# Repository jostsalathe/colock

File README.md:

# Colock
A USB powered RGB wall clock inspired by analog clocks

## Parts

| Part | Count | Refs | JLCPCB # ***extended*** |
| --- | --- | --- | --- |
| 100nF | 61 | C1...60, C63 | C14663 |
| 10uF | 2 | C61, C62 | C19702 |
| SK6812SIDE-A-RVS | 60 | LED1...60 | ***C2890037*** |
| TYPE-C-31-M-17 | 1 | J15 | ***C283540*** |
| AO3400A | 1 | Q1 | C20917 |
| 0R | 1 | R1 | C21189 |
| 2k2 | 1 | R2 | C4190 |
| 10k | 4 | R3...6 | C25804 |
| 5k1 | 2 | R7, R8 | C23186 |
| AMS1117-3.3 | 1 | U1 | C6186 |

## Assembly

You need two panels with one main segment and five LED segments each to for a full circle by soldering all those segments together.

The panels should look a little something like this (don't mind the missing 3D models):

One of the two main segments needs to get the USB-C socket, (optionally the UART header) as well as the ESP-01 Pin-Socket added and the 0 Ohm link R1 removed (if ordered with populated SMD components).

The other main segment may benefit from removing the pullup resistor R2 and the level shifting MOSFET Q1.

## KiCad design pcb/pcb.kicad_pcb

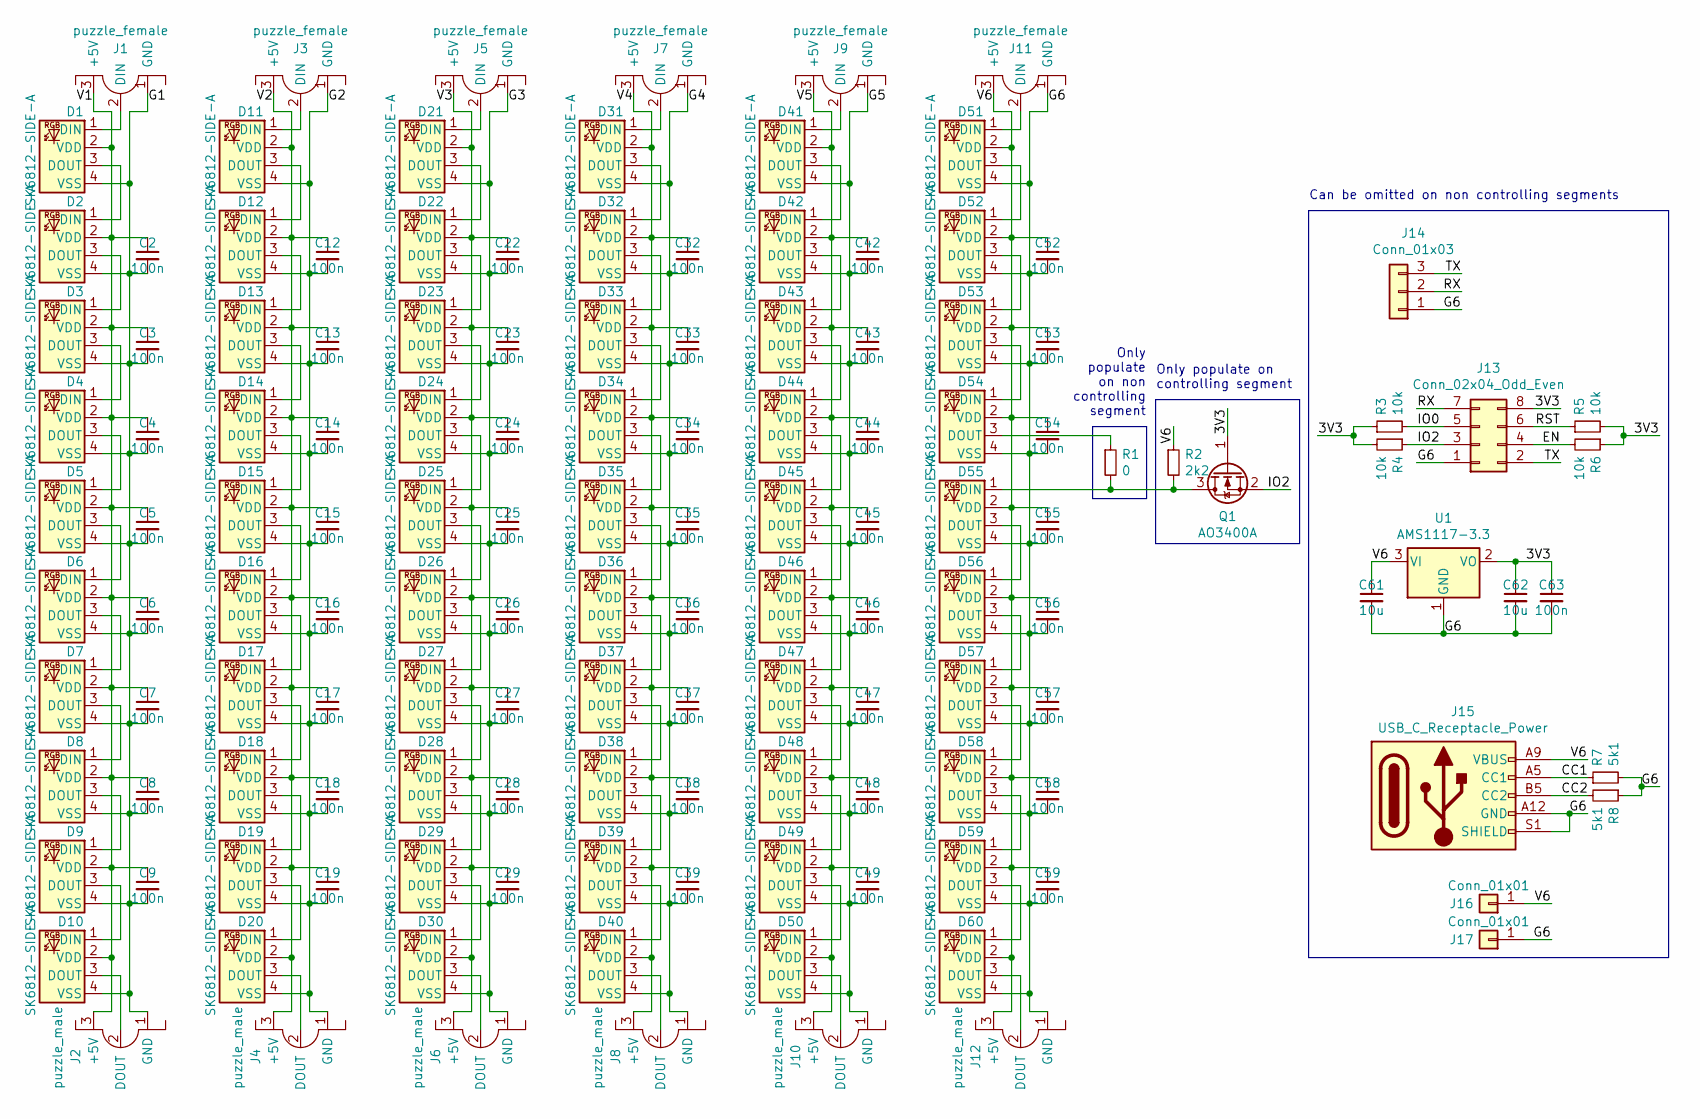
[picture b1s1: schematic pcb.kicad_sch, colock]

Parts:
C2, C3, C4, C5, C6, C7, C8, C9, C12, C13, C14, C15, C16, C17, C18, C19, C22, C23, C24, C25, C26, C27, C28, C29, C32, C33, C34, C35, C36, C37, C38, C39, C42, C43, C44, C45, C46, C47, C48, C49, C52, C53, C54, C55, C56, C57, C58, C59, C63: 100n; C_0603_1608Metric_Pad1.08x0.95mm_HandSolder
C61, C62: 10u; C_0603_1608Metric_Pad1.08x0.95mm_HandSolder
D1, D2, D3, D4, D5, D6, D7, D8, D9, D10, D11, D12, D13, D14, D15, D16, D17, D18, D19, D20, D21, D22, D23, D24, D25, D26, D27, D28, D29, D30, D31, D32, D33, D34, D35, D36, D37, D38, D39, D40, D41, D42, D43, D44, D45, D46, D47, D48, D49, D50, D51, D52, D53, D54, D55, D56, D57, D58, D59, D60: SK6812-SIDE-A; SK6812-SIDE-A_join_APA106-F8
J1, J3, J5, J7, J9, J11: puzzle_female
J2, J4, J6, J8, J10, J12: puzzle_male
J13: Conn_02x04_Odd_Even; PinSocket_2x04_P2.54mm_Vertical
J14: Conn_01x03; PinHeader_1x03_P2.54mm_Vertical
J15: USB_C_Receptacle_Power; USB_C_Receptacle_HRO_TYPE-C-31-M-17
J16, J17: Conn_01x01; TestPoint_Pad_2.5x2.5mm
Q1: AO3400A; SOT-23
R1: 0; R_0603_1608Metric_Pad1.05x0.95mm_HandSolder
R2: 2k2; R_0603_1608Metric_Pad1.05x0.95mm_HandSolder
R3, R4, R5, R6: 10k; R_0603_1608Metric_Pad1.05x0.95mm_HandSolder
R7, R8: 5k1; R_0603_1608Metric_Pad1.05x0.95mm_HandSolder
U1: AMS1117-3.3; SOT-223-3_TabPin2

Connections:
/3V3: C62.1, C63.1, J13.8, Q1.1 (G), R3.1, R4.2, R5.2, R6.1, U1.2 (VO)
/CC1: J15.A5 (CC1), R7.1
/CC2: J15.B5 (CC2), R8.2
/EN: J13.4, R6.2
/G1: C2.2, C3.2, C4.2, C5.2, C6.2, C7.2, C8.2, C9.2, D1.4 (VSS), D2.4 (VSS), D3.4 (VSS), D4.4 (VSS), D5.4 (VSS), D6.4 (VSS), D7.4 (VSS), D8.4 (VSS), D9.4 (VSS), D10.4 (VSS), J1.1 (GND), J2.1 (GND)
/G2: C12.2, C13.2, C14.2, C15.2, C16.2, C17.2, C18.2, C19.2, D11.4 (VSS), D12.4 (VSS), D13.4 (VSS), D14.4 (VSS), D15.4 (VSS), D16.4 (VSS), D17.4 (VSS), D18.4 (VSS), D19.4 (VSS), D20.4 (VSS), J3.1 (GND), J4.1 (GND)
/G3: C22.2, C23.2, C24.2, C25.2, C26.2, C27.2, C28.2, C29.2, D21.4 (VSS), D22.4 (VSS), D23.4 (VSS), D24.4 (VSS), D25.4 (VSS), D26.4 (VSS), D27.4 (VSS), D28.4 (VSS), D29.4 (VSS), D30.4 (VSS), J5.1 (GND), J6.1 (GND)
/G4: C32.2, C33.2, C34.2, C35.2, C36.2, C37.2, C38.2, C39.2, D31.4 (VSS), D32.4 (VSS), D33.4 (VSS), D34.4 (VSS), D35.4 (VSS), D36.4 (VSS), D37.4 (VSS), D38.4 (VSS), D39.4 (VSS), D40.4 (VSS), J7.1 (GND), J8.1 (GND)
/G5: C42.2, C43.2, C44.2, C45.2, C46.2, C47.2, C48.2, C49.2, D41.4 (VSS), D42.4 (VSS), D43.4 (VSS), D44.4 (VSS), D45.4 (VSS), D46.4 (VSS), D47.4 (VSS), D48.4 (VSS), D49.4 (VSS), D50.4 (VSS), J9.1 (GND), J10.1 (GND)
/G6: C52.2, C53.2, C54.2, C55.2, C56.2, C57.2, C58.2, C59.2, C61.2, C62.2, C63.2, D51.4 (VSS), D52.4 (VSS), D53.4 (VSS), D54.4 (VSS), D55.4 (VSS), D56.4 (VSS), D57.4 (VSS), D58.4 (VSS), D59.4 (VSS), D60.4 (VSS), J11.1 (GND), J12.1 (GND), J13.1, J14.1, J15.A12 (GND), J15.B12 (GND), J15.S1 (SHIELD), J17.1, R7.2, R8.1, U1.1 (GND)
/IO0: J13.5, R3.2
/IO2: J13.3, Q1.2 (S), R4.1
/RST: J13.6, R5.1
/RX: J13.7, J14.2
/TX: J13.2, J14.3
/V1: C2.1, C3.1, C4.1, C5.1, C6.1, C7.1, C8.1, C9.1, D1.2 (VDD), D2.2 (VDD), D3.2 (VDD), D4.2 (VDD), D5.2 (VDD), D6.2 (VDD), D7.2 (VDD), D8.2 (VDD), D9.2 (VDD), D10.2 (VDD), J1.3 (+5V), J2.3 (+5V)
/V2: C12.1, C13.1, C14.1, C15.1, C16.1, C17.1, C18.1, C19.1, D11.2 (VDD), D12.2 (VDD), D13.2 (VDD), D14.2 (VDD), D15.2 (VDD), D16.2 (VDD), D17.2 (VDD), D18.2 (VDD), D19.2 (VDD), D20.2 (VDD), J3.3 (+5V), J4.3 (+5V)
/V3: C22.1, C23.1, C24.1, C25.1, C26.1, C27.1, C28.1, C29.1, D21.2 (VDD), D22.2 (VDD), D23.2 (VDD), D24.2 (VDD), D25.2 (VDD), D26.2 (VDD), D27.2 (VDD), D28.2 (VDD), D29.2 (VDD), D30.2 (VDD), J5.3 (+5V), J6.3 (+5V)
/V4: C32.1, C33.1, C34.1, C35.1, C36.1, C37.1, C38.1, C39.1, D31.2 (VDD), D32.2 (VDD), D33.2 (VDD), D34.2 (VDD), D35.2 (VDD), D36.2 (VDD), D37.2 (VDD), D38.2 (VDD), D39.2 (VDD), D40.2 (VDD), J7.3 (+5V), J8.3 (+5V)
/V5: C42.1, C43.1, C44.1, C45.1, C46.1, C47.1, C48.1, C49.1, D41.2 (VDD), D42.2 (VDD), D43.2 (VDD), D44.2 (VDD), D45.2 (VDD), D46.2 (VDD), D47.2 (VDD), D48.2 (VDD), D49.2 (VDD), D50.2 (VDD), J9.3 (+5V), J10.3 (+5V)
/V6: C52.1, C53.1, C54.1, C55.1, C56.1, C57.1, C58.1, C59.1, C61.1, D51.2 (VDD), D52.2 (VDD), D53.2 (VDD), D54.2 (VDD), D55.2 (VDD), D56.2 (VDD), D57.2 (VDD), D58.2 (VDD), D59.2 (VDD), D60.2 (VDD), J11.3 (+5V), J12.3 (+5V), J15.A9 (VBUS), J15.B9 (VBUS), J16.1, R2.1, U1.3 (VI)
unnamed: D1.1 (DIN), J1.2 (DIN)
unnamed: D1.3 (DOUT), D2.1 (DIN)
unnamed: D2.3 (DOUT), D3.1 (DIN)
unnamed: D3.3 (DOUT), D4.1 (DIN)
unnamed: D4.3 (DOUT), D5.1 (DIN)
unnamed: D5.3 (DOUT), D6.1 (DIN)
unnamed: D6.3 (DOUT), D7.1 (DIN)
unnamed: D7.3 (DOUT), D8.1 (DIN)
unnamed: D8.3 (DOUT), D9.1 (DIN)
unnamed: D9.3 (DOUT), D10.1 (DIN)
unnamed: D10.3 (DOUT), J2.2 (DOUT)
unnamed: D11.1 (DIN), J3.2 (DIN)
unnamed: D11.3 (DOUT), D12.1 (DIN)
unnamed: D12.3 (DOUT), D13.1 (DIN)
unnamed: D13.3 (DOUT), D14.1 (DIN)
unnamed: D14.3 (DOUT), D15.1 (DIN)
unnamed: D15.3 (DOUT), D16.1 (DIN)
unnamed: D16.3 (DOUT), D17.1 (DIN)
unnamed: D17.3 (DOUT), D18.1 (DIN)
unnamed: D18.3 (DOUT), D19.1 (DIN)
unnamed: D19.3 (DOUT), D20.1 (DIN)
unnamed: D20.3 (DOUT), J4.2 (DOUT)
unnamed: D21.1 (DIN), J5.2 (DIN)
unnamed: D21.3 (DOUT), D22.1 (DIN)
unnamed: D22.3 (DOUT), D23.1 (DIN)
unnamed: D23.3 (DOUT), D24.1 (DIN)
unnamed: D24.3 (DOUT), D25.1 (DIN)
unnamed: D25.3 (DOUT), D26.1 (DIN)
unnamed: D26.3 (DOUT), D27.1 (DIN)
unnamed: D27.3 (DOUT), D28.1 (DIN)
unnamed: D28.3 (DOUT), D29.1 (DIN)
unnamed: D29.3 (DOUT), D30.1 (DIN)
unnamed: D30.3 (DOUT), J6.2 (DOUT)
unnamed: D31.1 (DIN), J7.2 (DIN)
unnamed: D31.3 (DOUT), D32.1 (DIN)
unnamed: D32.3 (DOUT), D33.1 (DIN)
unnamed: D33.3 (DOUT), D34.1 (DIN)
unnamed: D34.3 (DOUT), D35.1 (DIN)
unnamed: D35.3 (DOUT), D36.1 (DIN)
unnamed: D36.3 (DOUT), D37.1 (DIN)
unnamed: D37.3 (DOUT), D38.1 (DIN)
unnamed: D38.3 (DOUT), D39.1 (DIN)
unnamed: D39.3 (DOUT), D40.1 (DIN)
unnamed: D40.3 (DOUT), J8.2 (DOUT)
unnamed: D41.1 (DIN), J9.2 (DIN)
unnamed: D41.3 (DOUT), D42.1 (DIN)
unnamed: D42.3 (DOUT), D43.1 (DIN)
unnamed: D43.3 (DOUT), D44.1 (DIN)
unnamed: D44.3 (DOUT), D45.1 (DIN)
unnamed: D45.3 (DOUT), D46.1 (DIN)
unnamed: D46.3 (DOUT), D47.1 (DIN)
unnamed: D47.3 (DOUT), D48.1 (DIN)
unnamed: D48.3 (DOUT), D49.1 (DIN)
unnamed: D49.3 (DOUT), D50.1 (DIN)
unnamed: D50.3 (DOUT), J10.2 (DOUT)
unnamed: D51.1 (DIN), J11.2 (DIN)
unnamed: D51.3 (DOUT), D52.1 (DIN)
unnamed: D52.3 (DOUT), D53.1 (DIN)
unnamed: D53.3 (DOUT), D54.1 (DIN)
unnamed: D54.3 (DOUT), R1.1
unnamed: D55.1 (DIN), Q1.3 (D), R1.2, R2.2
unnamed: D55.3 (DOUT), D56.1 (DIN)
unnamed: D56.3 (DOUT), D57.1 (DIN)
unnamed: D57.3 (DOUT), D58.1 (DIN)
unnamed: D58.3 (DOUT), D59.1 (DIN)
unnamed: D59.3 (DOUT), D60.1 (DIN)
unnamed: D60.3 (DOUT), J12.2 (DOUT)

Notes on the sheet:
Only populate on controlling segment
Can be omitted on non controlling segments
Only populate on non controlling segment

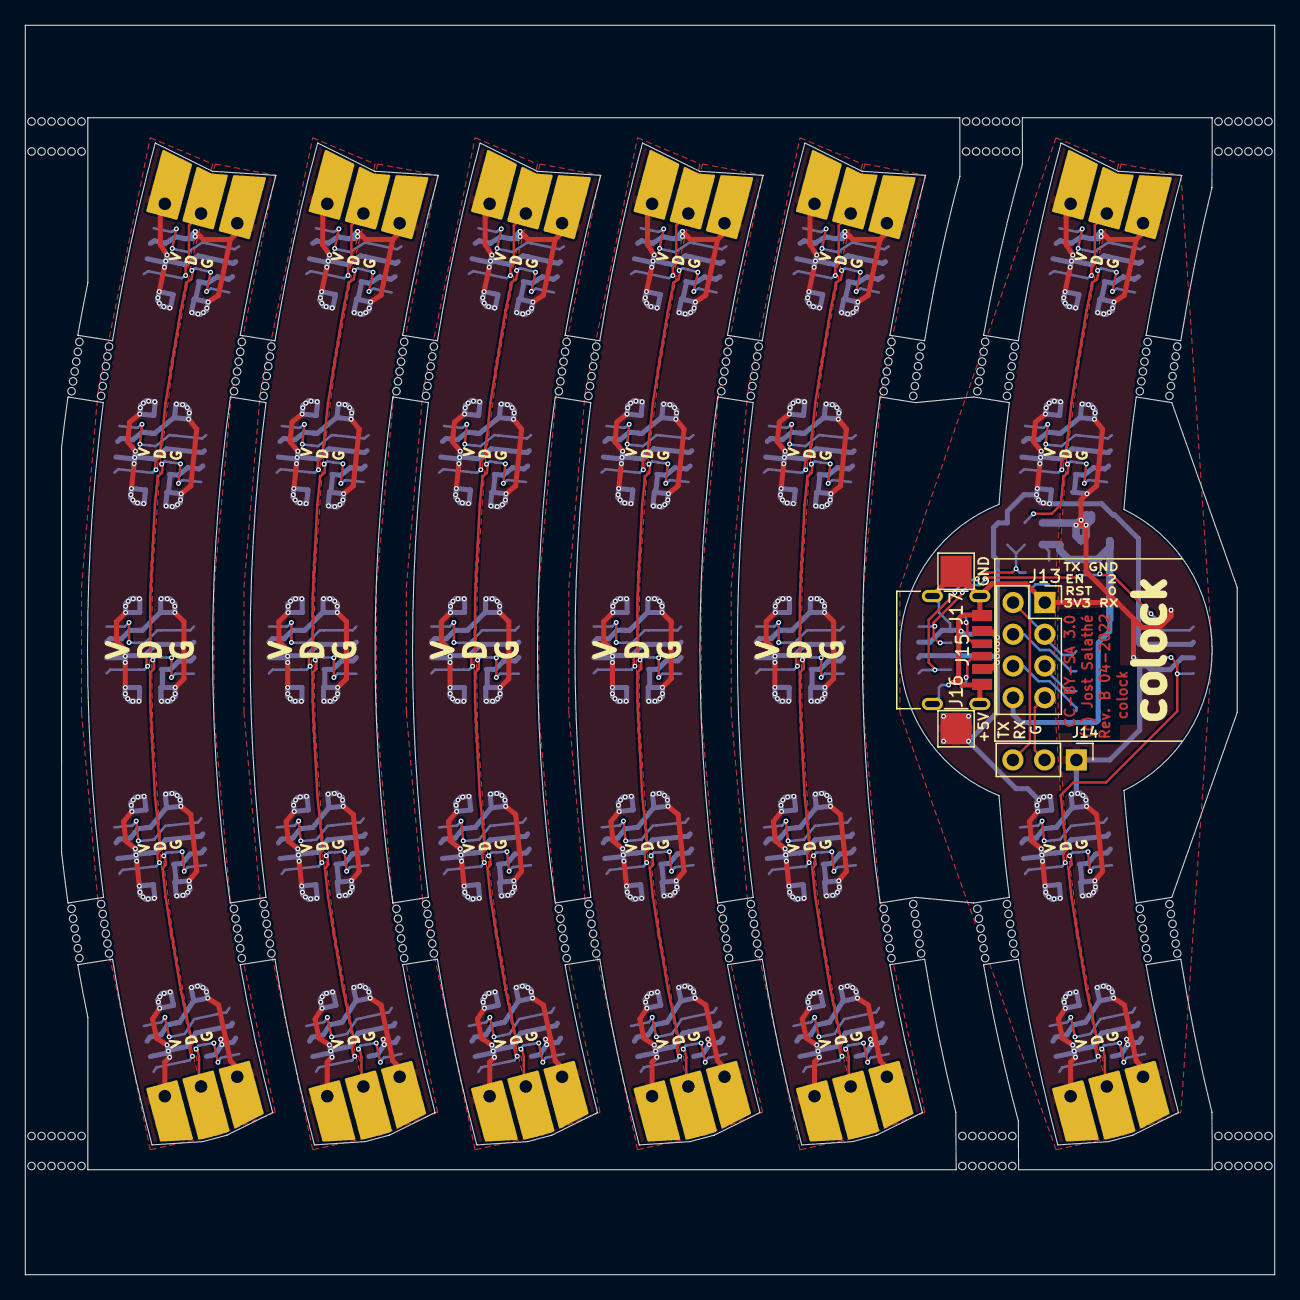
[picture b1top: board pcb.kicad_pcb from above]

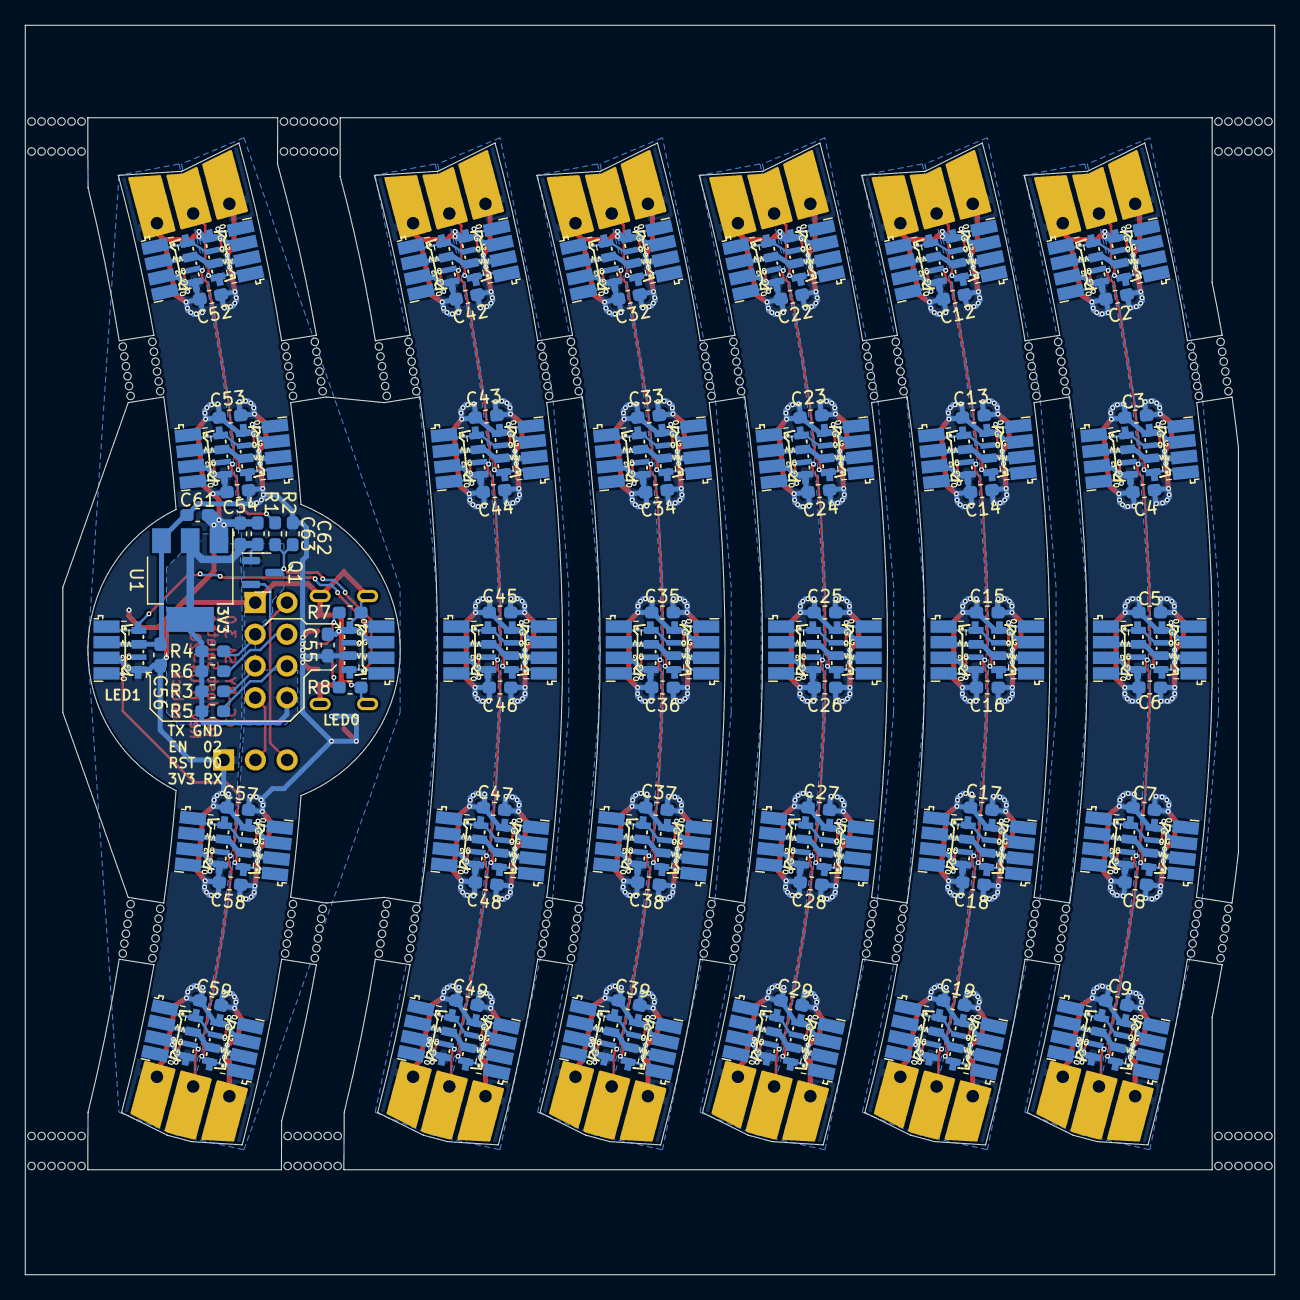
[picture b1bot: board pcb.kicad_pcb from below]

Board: 2 copper layers, 100.0 x 100.0 mm, 160 parts (121 on the bottom side), 88 nets.

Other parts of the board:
mouse-bite-3mm-slot, mouse-bite-3mm-slot#2, mouse-bite-3mm-slot#3, mouse-bite-3mm-slot#4, mouse-bite-3mm-slot#5, mouse-bite-3mm-slot#6, mouse-bite-3mm-slot#7, mouse-bite-3mm-slot#8, mouse-bite-3mm-slot#9, mouse-bite-3mm-slot#10, mouse-bite-3mm-slot#11, mouse-bite-3mm-slot#12, mouse-bite-3mm-slot#13, mouse-bite-3mm-slot#14, mouse-bite-3mm-slot#15, mouse-bite-3mm-slot#16, mouse-bite-3mm-slot#17, mouse-bite-3mm-slot#18, mouse-bite-3mm-slot#19, mouse-bite-3mm-slot#20, mouse-bite-3mm-slot#21, mouse-bite-3mm-slot#22: VAL**; mouse-bite-3mm-slot

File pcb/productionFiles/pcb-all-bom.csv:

Comment,Designator,Footprint,LCSC
"100n","C1,C2,C3,C4,C5,C6,C7,C8,C9,C10,C11,C12,C13,C14,C15,C16,C17,C18,C19,C20,C21,C22,C23,C24,C25,C26,C27,C28,C29,C30,C31,C32,C33,C34,C35,C36,C37,C38,C39,C40,C41,C42,C43,C44,C45,C46,C47,C48,C49,C50,C51,C52,C53,C54,C55,C56,C57,C58,C59,C60,C63","Capacitor_SMD:C_0603_1608Metric_Pad1.08x0.95mm_HandSolder","C14663"
"10u","C61,C62","Capacitor_SMD:C_0603_1608Metric_Pad1.08x0.95mm_HandSolder","C19702"
"WS2812B-4020","D1,D2,D3,D4,D5,D6,D7,D8,D9,D10,D11,D12,D13,D14,D15,D16,D17,D18,D19,D20,D21,D22,D23,D24,D25,D26,D27,D28,D29,D30,D31,D32,D33,D34,D35,D36,D37,D38,D39,D40,D41,D42,D43,D44,D45,D46,D47,D48,D49,D50,D51,D52,D53,D54,D55,D56,D57,D58,D59,D60","myLibrary:WS2812B-4020","C965557"
"puzzle_female","J1,J3,J5,J7,J9,J11","myLibrary:puzzle_female",""
"Conn_02x04_Odd_Even","J13","Connector_PinSocket_2.54mm:PinSocket_2x04_P2.54mm_Vertical",""
"Conn_01x03","J14","Connector_PinHeader_2.54mm:PinHeader_1x03_P2.54mm_Vertical",""
"USB_C_Receptacle_Power","J15","myLibrary:USB_C_Receptacle_HRO_TYPE-C-31-M-17","C283540"
"puzzle_male","J2,J4,J6,J8,J10,J12","myLibrary:puzzle_male",""
"AO3400A","Q1","Package_TO_SOT_SMD:SOT-23","C20917"
"0","R1","Resistor_SMD:R_0603_1608Metric_Pad1.05x0.95mm_HandSolder","C21189"
"2k2","R2","Resistor_SMD:R_0603_1608Metric_Pad1.05x0.95mm_HandSolder","C4190"
"10k","R3,R4,R5,R6","Resistor_SMD:R_0603_1608Metric_Pad1.05x0.95mm_HandSolder","C25804"
"5k1","R7,R8","Resistor_SMD:R_0603_1608Metric_Pad1.05x0.95mm_HandSolder","C23186"
"AMS1117-3.3","U1","Package_TO_SOT_SMD:SOT-223-3_TabPin2","C6186"

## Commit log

2021-11-03 messing around
2021-11-04 tweaked the concepts a little
2021-11-05 started parts list in README.md
2021-11-05 correction
2021-11-07 worked on controller schematics
2021-11-08 Added level shifter for LEDs
2021-11-09 Done with the layout in general. Mouse bites and edge rails still missing.
2021-11-15 Added rails and mouse bites for production. Someone with some experience with those should take a look at them before I move on, though...
2021-11-17 Added some text to breakaway tabs and modified mouse bite footprint a little.
2021-11-18 Started work on firmware.
2021-11-20 Worked on proof of concept firmware
2021-11-23 Finishing touches on PCB
2021-11-24 Finalized Rev. A and added production files.
2021-11-24 Removed unnecessary and not working TOC section from README.md.
2022-02-26 Using the ESP8266 Arduino Core v2.6.3, this demo firmware should now compile and work.
2022-02-26 Using the ESP8266 Arduino Core v2.6.3, this demo firmware should now compile and work. This time for realz...
2022-02-26 Using NeoPixelBus now because it works properly with newer ESP8266 Arduino Core versions.
2022-03-14 Migrated pcb files to KiCAD 6.
2022-03-14 #1: Reshaped segment interconnects and added solder pads for 5V input.
2022-03-15 Worked on SK6812-SIDE-A_join_APA106-F8.kicad_mod
2022-03-15 Worked on footprints.
2022-03-16 Cleanup of now obsolete copper traces and areas.
2022-03-16 Redesigned copper areas.
2022-03-17 Routing for dumb segments done. Also worked on routing of controller segment.
2023-05-14 finished routing the uC section so now the PCB should be complete. New production files not generated, yet.

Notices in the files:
pcb/pcb.kicad_pcb:
CC-BY-SA 3.0
